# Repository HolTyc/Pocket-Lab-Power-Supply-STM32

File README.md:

# Pocket Lab Power Supply with STM32 MCU

THIS IS A FORK AND THE ORIGINAL VERSION IS HERE: https://github.com/BenMakesEverything/Pocket-Lab-Power-Supply/tree/main
A lab bench power supply, but pocket-sized and battery powered. (This repo is currently WIP)
The main MCU is STM32L031G6U6 for longer battery life.

## What it is:

A 4S Lithium Ion-based Battery Bank which can act as a portable Lab-Bench Power Supply. Designed for use with 4S lithium-ion battery packs.

## Features:

- Adjustable output voltage and current limit
- Battery powered
- USB-C/PD charging
- 0.91 OLED display
- Open hardware and firmware

## Repository Structure:

- `/hardware` - PCB, schematic, BOM, Gerbers, CAD
- `/firmware` - MCU firmware and utilities
- `/docs` - build guide, diagrams, images, notes (WIP)

## Parts List

- Main PCB
- "Backpack" PCB for Display Module
- Display: HCMS-2971 or HCMS-2972 or HCMS-2973 or HCMS-2974 or HCMS-2975
- 4S 21700 Battery with integrated BMS (XH2.54mm connector) [LINK](https://www.foxbuying.com/21700-14-8v-4s1p-4500mah-rechargeable-power-lithium-battery-pack-with-customised-connetor.html)
- Faceplate
- 3D Printable Body
- 4x M3 Threaded Inserts
- 4x M3 Hex-head/socket bolts (16mm threaded portion)
- Plastic cap for button
- Encoder Knob [LINK](https://www.adafruit.com/product/5531)

## Documentation:

For common questions, see the [FAQ](docs/FAQ.md). This is a work in progress and I will add more.

The following flowchart gives an overview of the way the main components are connected.

## Safety Notice:

This project involves lithium-ion batteries and power electronics. Build and use at your own risk.

The PCB was designed for use with 4S battery packs. The BQ25792 will charge the pack up to 16.8V.

IF YOU WANT TO USE ANOTHER CELL CONFIGURATION YOU MUST CHANGE THIS! OTHERWISE THE CELLS WILL BE OVERCHARGED AND DAMAGED!

(Pin 20 "PROG" on the BQ25792 is the thing you need to adjust.)

YOU MUST USE A PACK THAT CONTAINS A BMS! THIS DESIGN DOES NOT INCLUDE ONE.

## License!

This project is licensed under the CERN Open Hardware Licence Version 2 - Strongly Reciprocal, CERN-OHL-S-2.0.

Unless otherwise stated, this applies to all hardware design files, firmware, software utilities, documentation, images, diagrams, CAD files, manufacturing files, and other project files in this repository.

Commercial use is allowed under the terms of the license. The project name, author name, logo, branding, and media identity are not licensed for use in marketing or endorsement without permission.

See `LICENSE.txt` for the full license text.

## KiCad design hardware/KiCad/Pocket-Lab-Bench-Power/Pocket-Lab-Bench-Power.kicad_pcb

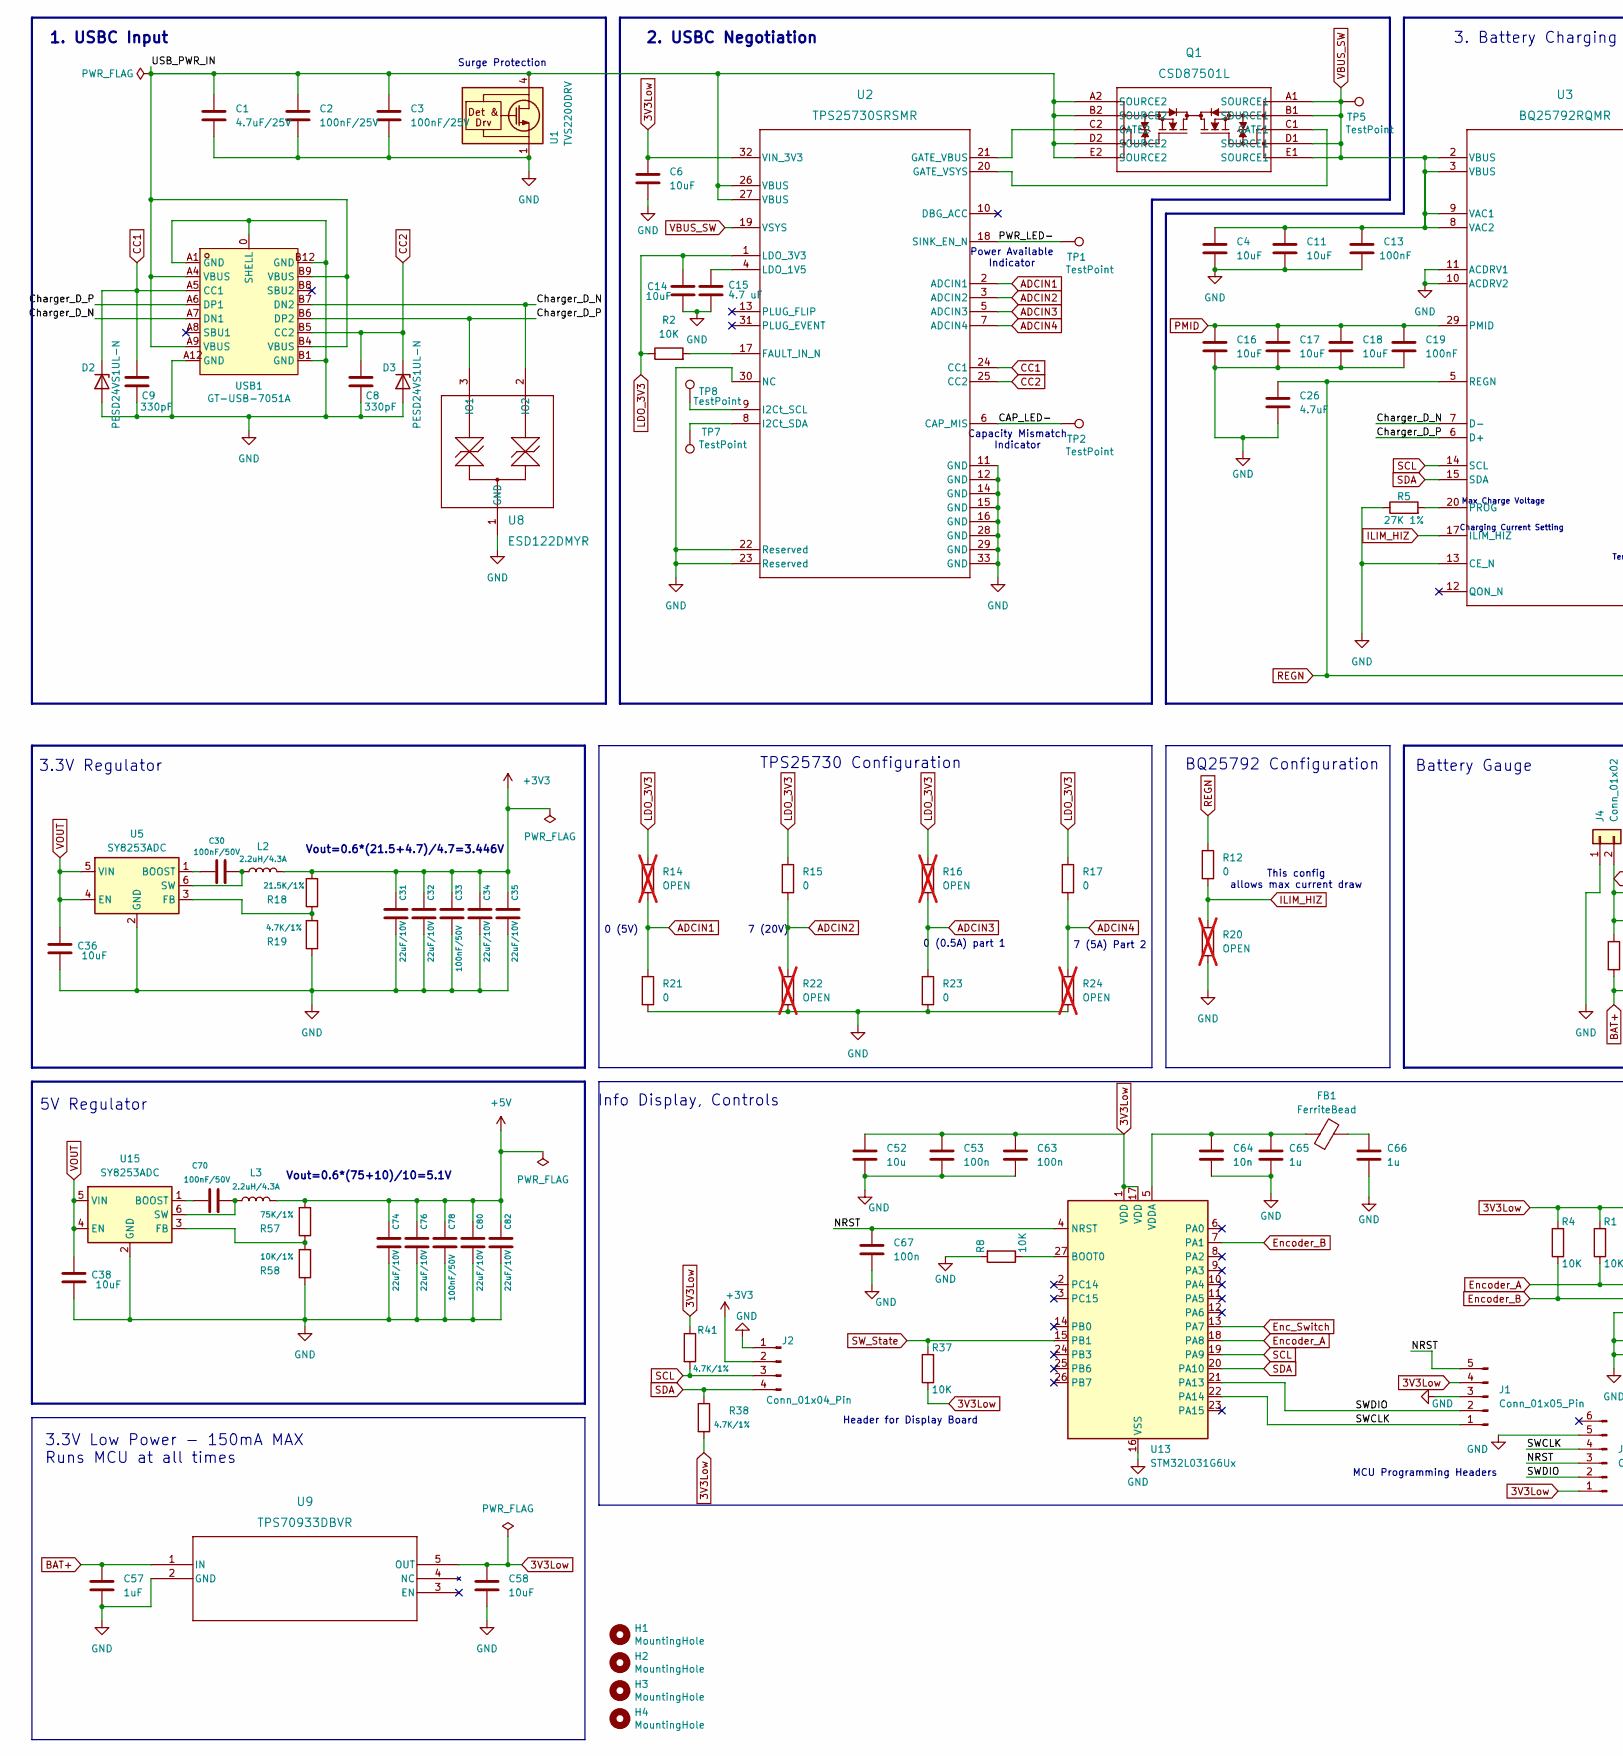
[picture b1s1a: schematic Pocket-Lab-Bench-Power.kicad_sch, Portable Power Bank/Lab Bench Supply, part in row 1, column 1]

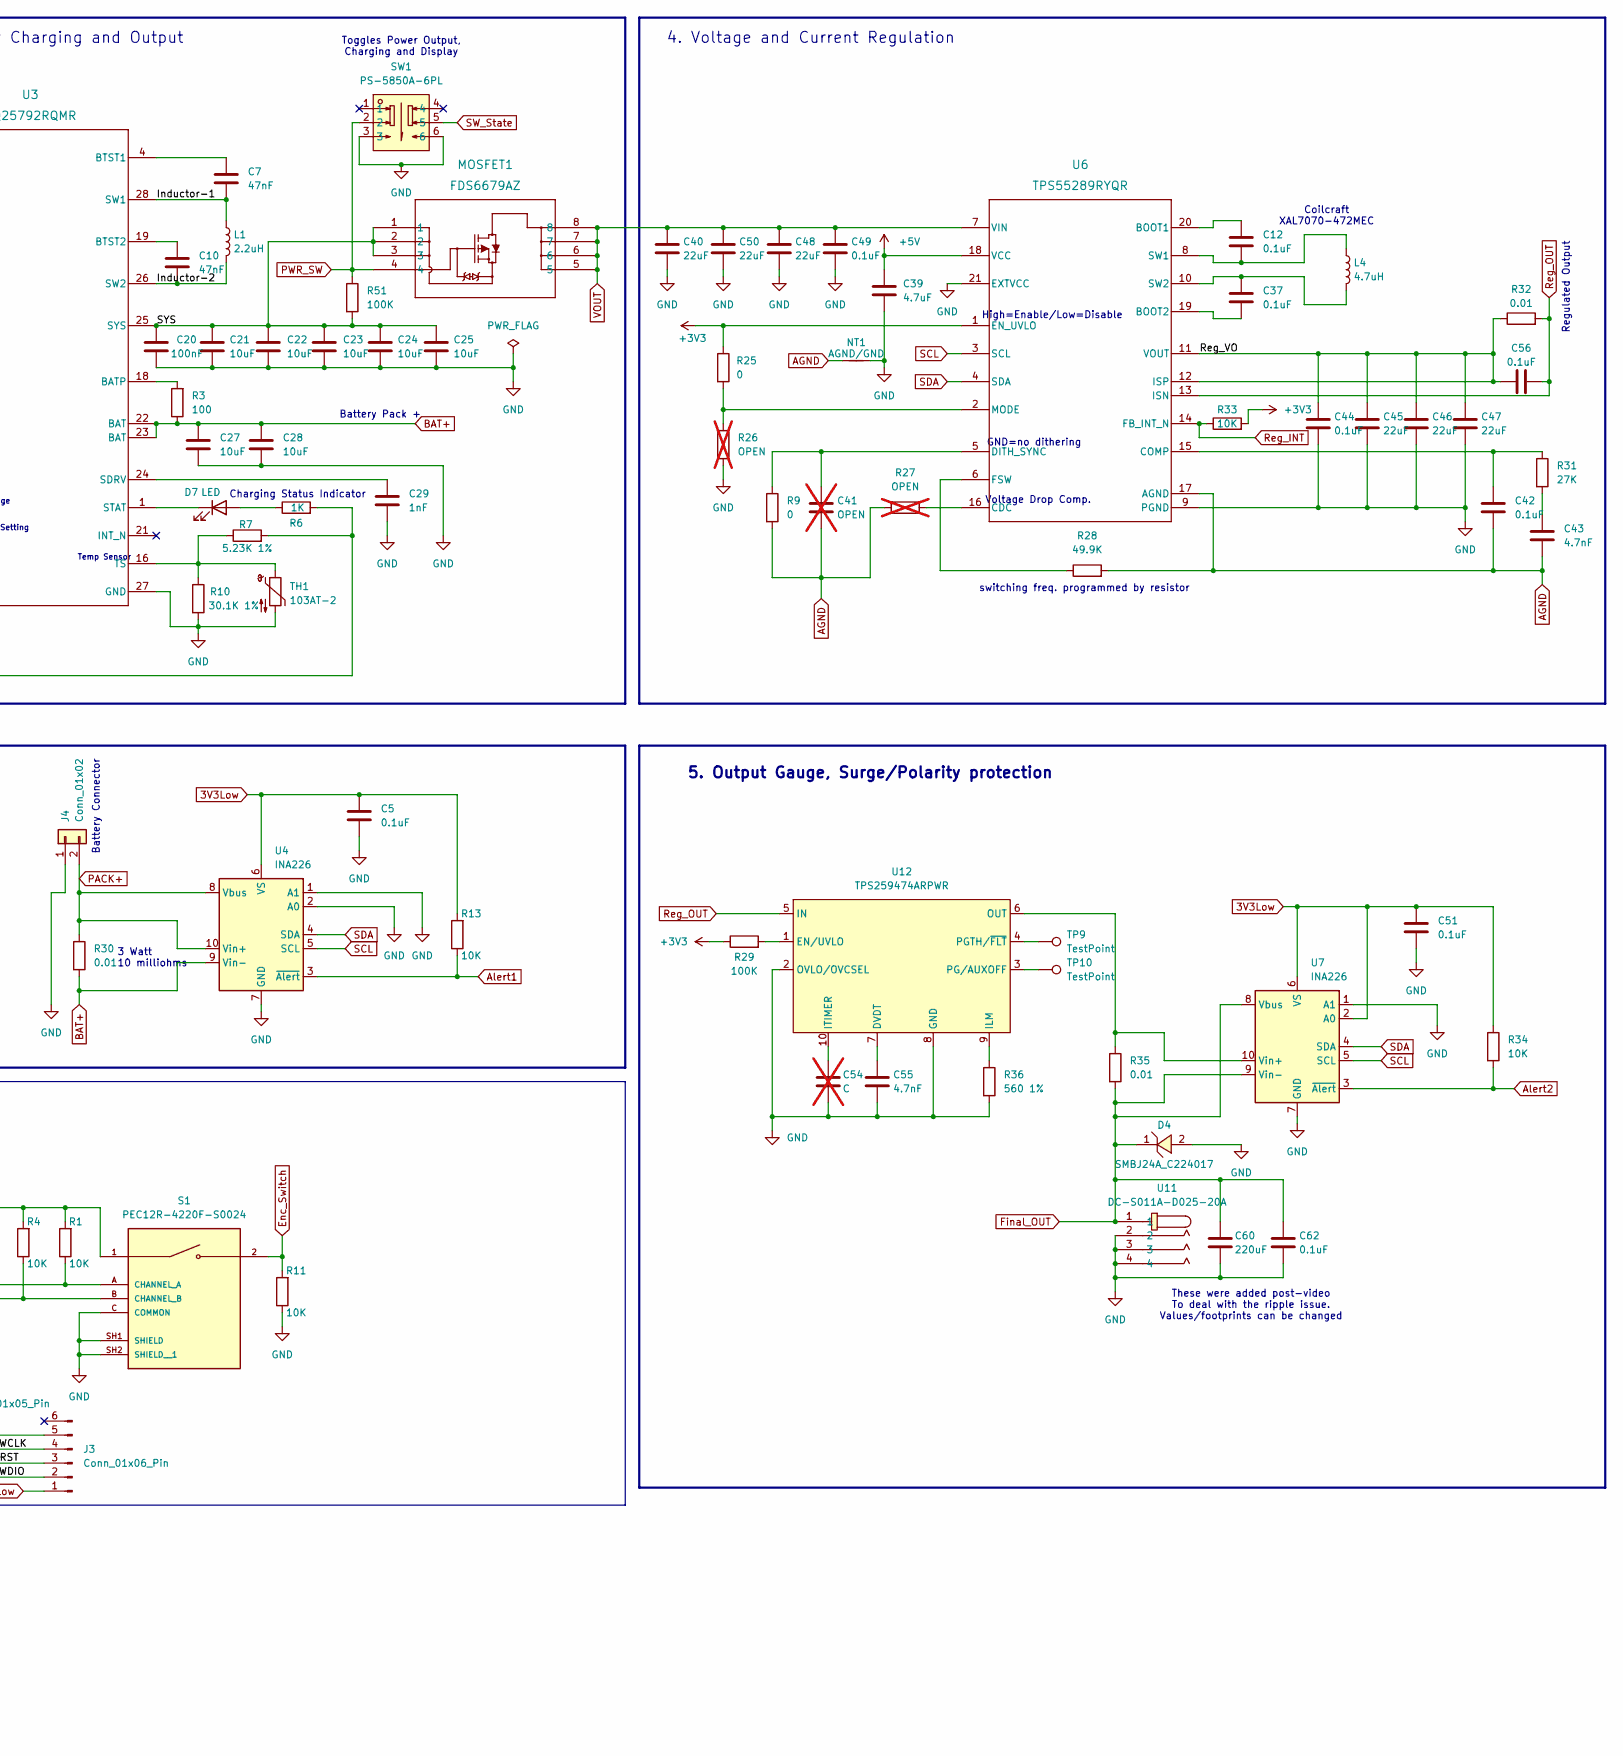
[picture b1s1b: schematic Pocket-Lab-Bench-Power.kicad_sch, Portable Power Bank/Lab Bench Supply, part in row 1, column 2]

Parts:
C1: 4.7uF/25V; C_0603_1608Metric
C2, C3: 100nF/25V; C_0603_1608Metric
C4, C11, C16, C17, C18, C21, C22, C23, C24, C25, C27, C28: 10uF; C_0805_2012Metric
C5, C12, C37, C42, C44, C49, C51, C56: 0.1uF; C_0402_1005Metric
C6, C14, C58: 10uF; C_0402_1005Metric
C7, C10: 47nF; C_0402_1005Metric
C8, C9: 330pF; C_0402_1005Metric
C13, C19, C20: 100nF; C_0402_1005Metric
C15: 4.7 uF; C_0402_1005Metric
C26: 4.7uF; C_0603_1608Metric; Voltage Req 10V
C29: 1nF; C_0402_1005Metric
C30, C33, C70, C78: 100nF/50V; C_0603_1608Metric
C31, C32, C34, C35, C74, C76, C80, C82: 22uF/10V; C_0603_1608Metric
C36, C38: 10uF; C_0603_1608Metric
C39: 4.7uF; C_0603_1608Metric
C40, C45, C46, C47, C48, C50: 22uF; C_0603_1608Metric
C41: OPEN; C_0603_1608Metric; not fitted
C43: 4.7nF; C_0402_1005Metric
C52: 10u; C_0603_1608Metric; LCSC C19702
C53, C63, C67: 100n; C_0402_1005Metric; LCSC C1525
C54: C; C_0603_1608Metric; not fitted
C55: 4.7nF; C_0603_1608Metric
C57: 1uF; C_0603_1608Metric
C60: 220uF; C_1206_3216Metric; LCSC C412252
C62: 0.1uF; C_0603_1608Metric
C64: 10n; C_0402_1005Metric; LCSC C15195
C65, C66: 1u; C_0402_1005Metric; LCSC C52923
D2, D3: PESD24VS1UL-N; DFN1006-2L-RD; LCSC Part C406227
D4: SMBJ24A_C224017; SMB_L4.3-W3.6-LS5.4-RD; MPN SMBJ24A; LCSC Part C224017
D7: LED; LED_0603_1608Metric; LCSC Part C72038
FB1: FerriteBead; L_0603_1608Metric; LCSC C1002
H1, H2, H3, H4: MountingHole; MountingHole_3.2mm_M3
J1: Conn_01x05_Pin; PinHeader_1x05_P2.54mm_Vertical
J2: Conn_01x04_Pin; PinHeader_1x04_P2.54mm_Vertical; LCSC Part C2691448
J3: Conn_01x06_Pin; Edge_Connect_6
J4: Conn_01x02; JST_PH_B2B-PH-K_1x02_P2.00mm_Vertical; LCSC Part C495685
L1: 2.2uH; IND-SMD_L7.0-W6.6_MCW-0650-220; LCSC Part C5349701
L2, L3: 2.2uH/4.3A; L_Sunlord_SWPA4020S; LCSC Part C3222957
L4: 4.7uH; IND-SMD_L7.5-W7.2-1; LCSC Part C3911513
MOSFET1: FDS6679AZ; SOIC8_751EB_ONS; LCSC Part C116730
NT1: AGND/GND; NetTie-2_SMD_Pad0.5mm
Q1: CSD87501L; PICOSTAR-YJG_TEX; LCSC Part C2841784
R1, R4, R8, R11, R13, R37: 10K; R_0402_1005Metric; LCSC C25744
R2, R33, R34: 10K; R_0402_1005Metric
R3: 100; R_0603_1608Metric
R5: 27K 1%; R_0603_1608Metric
R6: 1K; R_0603_1608Metric
R7: 5.23K 1%; R_0603_1608Metric
R9, R12, R15, R17, R21, R23, R25: 0; R_0603_1608Metric
R10: 30.1K 1%; R_0603_1608Metric
R14, R16, R20, R22, R24, R26, R27: OPEN; R_0603_1608Metric; not fitted
R18: 21.5K/1%; R_0603_1608Metric
R19, R38, R41: 4.7K/1%; R_0603_1608Metric
R28: 49.9K; R_0603_1608Metric
R29, R51: 100K; R_0603_1608Metric
R30, R32, R35: 0.01; R_2512_6332Metric; LCSC Part C840621
R31: 27K; R_0402_1005Metric
R36: 560 1%; R_0603_1608Metric
R57: 75K/1%; R_0603_1608Metric
R58: 10K/1%; R_0603_1608Metric
S1: PEC12R-4220F-S0024; XDCR_PEC12R-4220F-S0024; PARTREV 07/21; LCSC Part C18164805
SW1: PS-5850A-6PL; SW-TH_6P-L5.8-W5.8-P2.00-LS4.5-BL_1; MPN PS-5850A-6PL; LCSC Part C963201
TH1: 103AT-2; PinHeader_1x02_P2.54mm_Vertical
TP1, TP2, TP5, TP7, TP8, TP9, TP10: TestPoint; TestPoint_Pad_D1.5mm
U1: TVS2200DRV; WSON-6-1EP_2x2mm_P0.65mm_EP1x1.6mm; LCSC Part C523793
U2: TPS25730SRSMR; RSM0032B-IPC_A; LCSC Part C22390380
U3: BQ25792RQMR; BQ25792; LCSC Part C2862876
U4: INA226; VSSOP-10_3x3mm_P0.5mm
U5, U15: SY8253ADC; TSOT-23-6; LCSC Part C93736
U6: TPS55289RYQR; RYQ0021A-MFG; LCSC Part C5942077
U7: INA226; VSSOP-10_3x3mm_P0.5mm; LCSC Part C49851
U8: ESD122DMYR; DMY0003A; LCSC Part C1975871
U9: TPS70933DBVR; DBV5_TEX; LCSC Part C89347
U11: DC-S011A-D025-20A; AUDIO-TH_DC-S011A-D025-20A; MPN DC-S011A-D025-20A; LCSC Part C7464915
U12: TPS259474ARPWR; VQFN-10_L2.0-W2.0-P0.45-TL; MPN TPS259474ARPWR; LCSC Part C3662807
U13: STM32L031G6Ux; QFN-28_4x4mm_P0.5mm; LCSC C96514
USB1: GT-USB-7051A; USB-C-SMD_GT-USB-7051A; MPN GT-USB-7051A; LCSC Part C2843970

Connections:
3V3Low: C5.1, C6.1, C51.1, C52.1, C53.1, C58.1, C63.1, J1.4, J3.1, R1.2, R4.2, R13.2, R34.1, R37.1, R38.2, R41.1, S1.1, U2.32 (VIN_3V3), U4.6 (VS), U7.2 (A0), U7.6 (VS), U9.5 (OUT), U13.1 (VDD), U13.17 (VDD)
+3V3: C31.2, C32.2, C33.1, C34.2, C35.2, J2.2, L2.2, R18.2, R25.1, R29.1, R33.2, U6.1 (EN_UVLO)
+5V: C39.1, C74.2, C76.2, C78.1, C80.2, C82.2, L3.2, R57.2, U6.18 (VCC)
/CAP_LED-: TP2.1 (1_1), U2.6 (CAP_MIS)
/Charger_D_N: U3.7 (D-), U8.2 (IO2), USB1.A7 (DN1), USB1.B7 (DN2)
/Charger_D_P: U3.6 (D+), U8.3 (IO1), USB1.A6 (DP1), USB1.B6 (DP2)
/Inductor-1: C7.2, L1.1, U3.28 (SW1)
/Inductor-2: C10.2, L1.2, U3.26 (SW2)
/NRST: C67.1, J1.5, J3.3, U13.4 (NRST)
/PWR_LED-: TP1.1 (1_1), U2.18 (SINK_EN_N)
/Reg_VO: C44.1, C45.1, C46.1, C47.1, C56.1, R32.1, U6.11 (VOUT), U6.12 (ISP)
/SWCLK: J1.1, J3.4, U13.22 (PA14)
/SWDIO: J1.2, J3.2, U13.21 (PA13)
/SYS: C20.1, C21.1, C22.1, C23.1, C24.1, C25.1, MOSFET1.1, MOSFET1.2, MOSFET1.3, R51.2, U3.25 (SYS)
/USB_PWR_IN: C1.1, C2.1, C3.1, Q1.A2 (SOURCE2), Q1.B2 (SOURCE2), Q1.D2 (SOURCE2), Q1.E2 (SOURCE2), U1.4 (IN), U1.5 (IN), U1.6 (IN), U2.26 (VBUS), U2.27 (VBUS), USB1.A4 (VBUS), USB1.A9 (VBUS), USB1.B4 (VBUS), USB1.B9 (VBUS)
ADCIN1: R14.2, R21.1, U2.2 (ADCIN1)
ADCIN2: R15.2, R22.1, U2.3 (ADCIN2)
ADCIN3: R16.2, R23.1, U2.5 (ADCIN3)
ADCIN4: R17.2, R24.1, U2.7 (ADCIN4)
AGND: C41.2, C42.2, C43.2, NT1.1, R9.2, R27.1, R28.2, U6.17 (AGND)
Alert1: R13.1, U4.3 (~Alert)
Alert2: R34.2, U7.3 (~Alert)
BAT+: C27.1, C28.1, C57.1, R3.1, R30.2, U3.22 (BAT), U3.23 (BAT), U4.9 (Vin-), U9.1 (IN)
CC1: C9.1, D2.1 (K), U2.24 (CC1), USB1.A5 (CC1)
CC2: C8.1, D3.1 (K), U2.25 (CC2), USB1.B5 (CC2)
Enc_Switch: R11.2, S1.2, U13.13 (PA7)
Encoder_A: R1.1, S1.A (CHANNEL_A), U13.18 (PA8)
Encoder_B: R4.1, S1.B (CHANNEL_B), U13.7 (PA1)
Final_OUT: C60.1, C62.1, D4.1, R35.2, U7.8 (Vbus), U7.9 (Vin-), U11.1
GND: C1.2, C2.2, C3.2, C4.1, C5.2, C6.2, C8.2, C9.2, C11.1, C13.2, C14.2, C15.2, C16.2, C17.2, C18.1, C19.2, C20.2, C21.2, C22.2, C23.2, C24.2, C25.2, C26.2, C27.2, C28.2, C29.2, C31.1, C32.1, C33.2, C34.1, C35.1, C36.2, C38.2, C39.2, C40.2, C44.2, C45.2, C46.2, C47.2, C48.2, C49.2, C50.2, C51.2, C52.2, C53.2, C54.2, C55.2, C57.2, C58.2, C60.2, C62.2, C63.2, C64.2, C65.1, C66.1, C67.2, C74.1, C76.1, C78.2, C80.1, C82.1, D2.2 (A), D3.2 (A), D4.2, J1.3, J2.1, J3.5, J4.1, NT1.2, R5.1, R8.2, R10.2, R11.1, R19.1, R20.2, R21.2, R22.2, R23.2, R24.2, R26.2, R36.2, R58.1, S1.C (COMMON), S1.SH1 (SHIELD), S1.SH2 (SHIELD__1), SW1.3, SW1.6, TH1.2, U1.1 (GND), U1.2 (GND), U1.3 (GND), U1.7 (GND), U2.11 (GND), U2.12 (GND), U2.14 (GND), U2.15 (GND), U2.16 (GND), U2.22 (Reserved), U2.23 (Reserved), U2.28 (GND), U2.29 (GND), U2.30 (NC), U2.33 (GND), U3.10 (ACDRV2), U3.11 (ACDRV1), U3.13 (CE_N), U3.27 (GND), U4.1 (A1), U4.2 (A0), U4.7 (GND), U5.2 (GND), U6.9 (PGND), U6.21 (EXTVCC), U7.1 (A1), U7.7 (GND), U8.1 (GND), U9.2 (GND), U11.2, U11.3, U11.4, U12.2 (OVLO/OVCSEL), U12.8 (GND), U13.16 (VSS), U13.28 (VSS), U15.2 (GND), USB1.0 (SHELL), USB1.A1 (GND), USB1.A12 (GND), USB1.B1 (GND), USB1.B12 (GND)
ILIM_HIZ: R12.2, R20.1, U3.17 (ILIM_HIZ)
LDO_3V3: C14.1, R2.1, R14.1, R15.1, R16.1, R17.1, U2.1 (LDO_3V3)
unnamed: C43.1, R31.2
unnamed: C66.2, FB1.2
unnamed: D7.2 (A), R6.1
unnamed: D7.1 (K), U3.1 (STAT)
unnamed: Q1.C1 (GATE1), U2.20 (GATE_VSYS)
unnamed: Q1.C2 (GATE2), U2.21 (GATE_VBUS)
unnamed: R2.2, U2.17 (FAULT_IN_N)
unnamed: TP8.1 (1_1), U2.9 (I2Ct_SCL)
unnamed: TP7.1 (1_1), U2.8 (I2Ct_SDA)
unnamed: C15.1, U2.4 (LDO_1V5)
unnamed: R3.2, U3.18 (BATP)
unnamed: C7.1, U3.4 (BTST1)
unnamed: C10.1, U3.19 (BTST2)
unnamed: R5.2, U3.20 (PROG)
unnamed: C29.1, U3.24 (SDRV)
unnamed: R7.1, R10.1, TH1.1, U3.16 (TS)
unnamed: C30.2, U5.1 (BOOST)
unnamed: R18.1, R19.2, U5.3 (FB)
unnamed: C30.1, L2.1, U5.6 (SW)
unnamed: C12.1, U6.20 (BOOT1)
unnamed: C37.2, U6.19 (BOOT2)
unnamed: R27.2, U6.16 (CDC)
unnamed: C42.1, R31.1, U6.15 (COMP)
unnamed: C41.1, R9.1, U6.5 (DITH_SYNC)
unnamed: R28.1, U6.6 (FSW)
unnamed: R25.2, R26.1, U6.2 (MODE)
unnamed: C12.2, L4.1, U6.8 (SW1)
unnamed: C37.1, L4.2, U6.10 (SW2)
unnamed: C55.1, U12.7 (DVDT)
unnamed: R29.2, U12.1 (EN/UVLO)
unnamed: R36.1, U12.9 (ILM)
unnamed: C54.1, U12.10 (ITIMER)
unnamed: R35.1, U7.10 (Vin+), U12.6 (OUT)
unnamed: TP9.1 (1_1), U12.4 (PGTH/~FLT)
unnamed: TP10.1 (1_1), U12.3 (PG/AUXOFF)
unnamed: R8.1, U13.27 (BOOT0)
unnamed: C64.1, C65.2, FB1.1, U13.5 (VDDA)
unnamed: C70.2, U15.1 (BOOST)
unnamed: R57.1, R58.2, U15.3 (FB)
unnamed: C70.1, L3.1, U15.6 (SW)
PACK+: J4.2, R30.1, U4.8 (Vbus), U4.10 (Vin+)
PMID: C16.1, C17.1, C18.2, C19.1, U3.29 (PMID)
PWR_SW: MOSFET1.4, R51.1, SW1.2
REGN: C26.1, R6.2, R7.2, R12.1, U3.5 (REGN)
Reg_INT: R33.1, U6.14 (FB_INT_N)
Reg_OUT: C56.2, R32.2, U6.13 (ISN), U12.5 (IN)
SCL: J2.3, R41.2, U3.14 (SCL), U4.5 (SCL), U6.3 (SCL), U7.5 (SCL), U13.19 (PA9)
SDA: J2.4, R38.1, U3.15 (SDA), U4.4 (SDA), U6.4 (SDA), U7.4 (SDA), U13.20 (PA10)
SW_State: R37.2, SW1.5, U13.15 (PB1)
VBUS_SW: C4.2, C11.2, C13.1, Q1.A1 (SOURCE1), Q1.B1 (SOURCE1), Q1.D1 (SOURCE1), Q1.E1 (SOURCE1), TP5.1 (1_1), U2.19 (VSYS), U3.2 (VBUS), U3.3 (VBUS), U3.8 (VAC2), U3.9 (VAC1)
VOUT: C36.1, C38.1, C40.1, C48.1, C49.1, C50.1, MOSFET1.5, MOSFET1.6, MOSFET1.7, MOSFET1.8, U5.4 (EN), U5.5 (VIN), U6.7 (VIN), U15.4 (EN), U15.5 (VIN)

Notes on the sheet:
Info Display, Controls
GND=no dithering
Battery Connector
4. Voltage and Current Regulation
Surge Protection
Voltage Drop Comp.
0 (5V)
switching freq. programmed by resistor
Battery Pack +
Charging Status Indicator
7 (20V)
BQ25792 Configuration
Temp Sensor
3.3V Regulator
Header for Display Board
Coilcraft XAL7070-472MEC
1. USBC Input
2. USBC Negotiation
TPS25730 Configuration
5. Output Gauge, Surge/Polarity protection
Regulated Output
3.3V Low Power - 150mA MAX Runs MCU at all times
3. Battery Charging and Output
7 (5A) Part 2
0 (0.5A) part 1
Capacity Mismatch Indicator
Charging Current Setting
These were added post-video To deal with the ripple issue. Values/footprints can be changed
Power Available Indicator
MCU Programming Headers
This config allows max current draw
Toggles Power Output, Charging and Display
3 Watt 10 milliohms
Max Charge Voltage
5V Regulator
Vout=0.6*(21.5+4.7)/4.7=3.446V
High=Enable/Low=Disable
Battery Gauge
Vout=0.6*(75+10)/10=5.1V

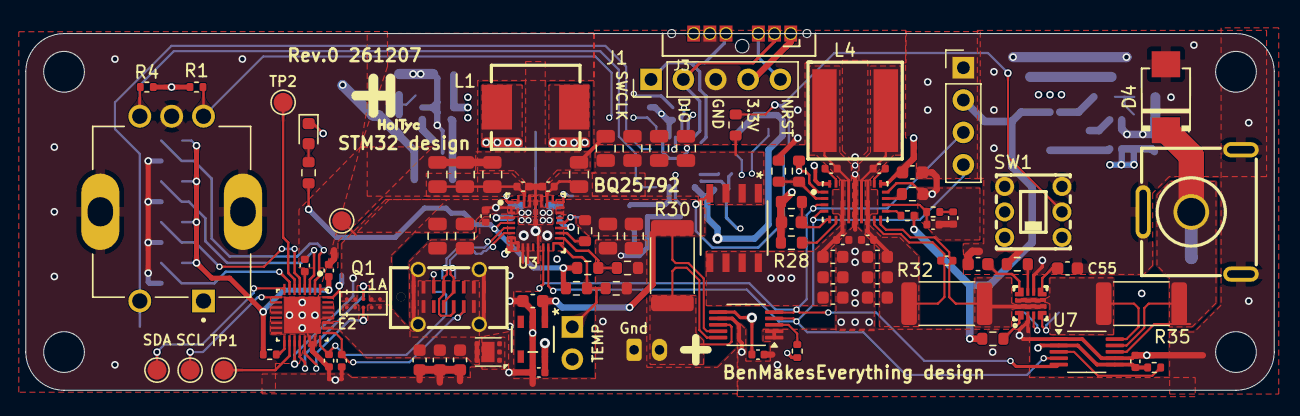
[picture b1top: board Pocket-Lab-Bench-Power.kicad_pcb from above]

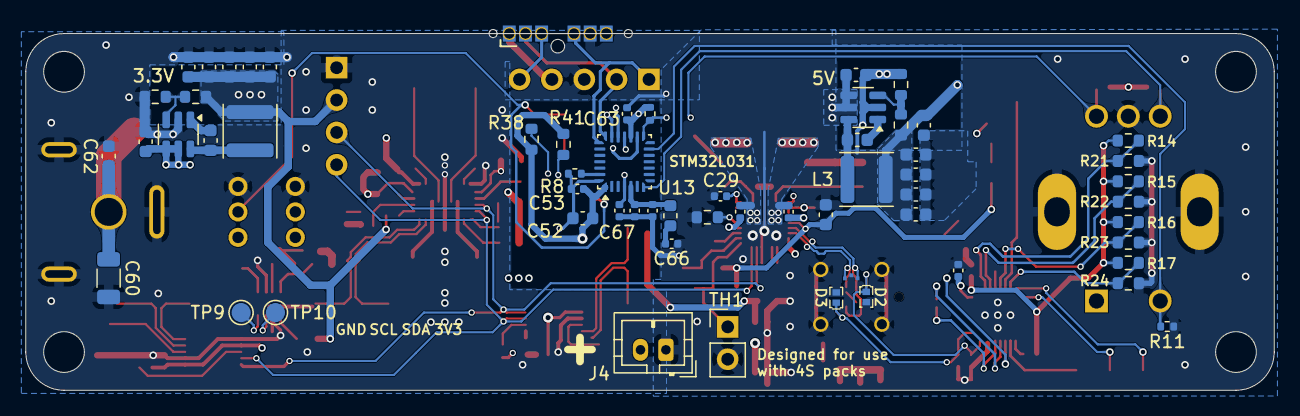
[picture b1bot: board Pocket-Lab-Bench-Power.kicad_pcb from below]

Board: 4 copper layers, 98.0 x 28.0 mm, 157 parts (59 on the bottom side), 83 nets.

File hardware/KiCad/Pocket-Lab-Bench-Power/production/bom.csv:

Designator,Footprint,Quantity,Value,LCSC Part #
C1,0603,1,4.7uF/25V,
"C10, C7",0402,2,47nF,
"C11, C16, C17, C18, C21, C22, C23, C24, C25, C27, C28, C4",0805,12,10uF,
"C12, C37, C42, C44, C49, C5, C51, C56",0402,8,0.1uF,
"C13, C19, C20",0402,3,100nF,
"C14, C58, C6",0402,3,10uF,
C15,0402,1,4.7 uF,
"C2, C3",0603,2,100nF/25V,
"C26, C39",0603,2,4.7uF,
C29,0402,1,1nF,
"C30, C33, C70, C78",0603,4,100nF/50V,
"C31, C32, C34, C35, C74, C76, C80, C82",0603,8,22uF/10V,
"C36, C38",0603,2,10uF,
"C40, C45, C46, C47, C48, C50",0603,6,22uF,
C43,0402,1,4.7nF,
C52,0603,1,10u,C19702
"C53, C63, C67",0402,3,100n,C1525
C55,0603,1,4.7nF,
C57,0603,1,1uF,
C60,1206,1,220uF,C412252
C62,0603,1,0.1uF,
C64,0402,1,10n,C15195
"C65, C66",0402,2,1u,C52923
"C8, C9",0402,2,330pF,
"D2, D3",DFN1006-2L-RD,2,PESD24VS1UL-N,C406227
D4,SMB_L4.3-W3.6-LS5.4-RD,1,SMBJ24A_C224017,C224017
D7,0603,1,LED,C72038
FB1,0603,1,FerriteBead,C1002
J1,PinHeader_1x05_P2.54mm_Vertical,1,Conn_01x05_Pin,
J2,PinHeader_1x04_P2.54mm_Vertical,1,Conn_01x04_Pin,C2691448
J3,Edge_Connect_6,1,Conn_01x06_Pin,
J4,JST_PH_B2B-PH-K_1x02_P2.00mm_Vertical,1,Conn_01x02,C495685
L1,IND-SMD_L7.0-W6.6_MCW-0650-220,1,2.2uH,C5349701
"L2, L3",L_Sunlord_SWPA4020S,2,2.2uH/4.3A,C3222957
L4,IND-SMD_L7.5-W7.2-1,1,4.7uH,C3911513
MOSFET1,SOIC8_751EB_ONS,1,FDS6679AZ,C116730
Q1,PICOSTAR-YJG_TEX,1,CSD87501L,C2841784
"R1, R11, R13, R37, R4, R8",0402,6,10K,C25744
R10,0603,1,30.1K 1%,
"R12, R15, R17, R21, R23, R25, R9",0603,7,0,
R18,0603,1,21.5K/1%,
"R19, R38, R41",0603,3,4.7K/1%,
"R2, R33, R34",0402,3,10K,
R28,0603,1,49.9K,
"R29, R51",0603,2,100K,
R3,0603,1,100,
"R30, R32, R35",2512,3,0.01,C840621
R31,0402,1,27K,
R36,0603,1,560 1%,
R5,0603,1,27K 1%,
R57,0603,1,75K/1%,
R58,0603,1,10K/1%,
R6,0603,1,1K,
R7,0603,1,5.23K 1%,
S1,XDCR_PEC12R-4220F-S0024,1,PEC12R-4220F-S0024,C18164805
SW1,SW-TH_6P-L5.8-W5.8-P2.00-LS4.5-BL_1,1,PS-5850A-6PL,C963201
TH1,PinHeader_1x02_P2.54mm_Vertical,1,103AT-2,
"TP10, TP7, TP8, TP9",TestPoint_Pad_D1.5mm,4,TestPoint,
U1,WSON-6-1EP_2x2mm_P0.65mm_EP1x1.6mm,1,TVS2200DRV,C523793
U11,AUDIO-TH_DC-S011A-D025-20A,1,DC-S011A-D025-20A,C7464915
U12,VQFN-10_L2.0-W2.0-P0.45-TL,1,TPS259474ARPWR,C3662807
U13,QFN-28_4x4mm_P0.5mm,1,STM32L031G6Ux,C96514
"U15, U5",TSOT-23-6,2,SY8253ADC,C93736
U2,RSM0032B-IPC_A,1,TPS25730SRSMR,C22390380
U3,BQ25792,1,BQ25792RQMR,C2862876
U4,VSSOP-10_3x3mm_P0.5mm,1,INA226,
U6,RYQ0021A-MFG,1,TPS55289RYQR,C5942077
U7,VSSOP-10_3x3mm_P0.5mm,1,INA226,C49851
U8,DMY0003A,1,ESD122DMYR,C1975871
U9,DBV5_TEX,1,TPS70933DBVR,C89347
USB1,USB-C-SMD_GT-USB-7051A,1,GT-USB-7051A,C2843970

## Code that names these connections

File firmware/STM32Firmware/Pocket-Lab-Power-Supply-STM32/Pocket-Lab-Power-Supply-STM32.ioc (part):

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Mcu.Name=STM32L031G(4-6)Ux
Mcu.Package=UFQFPN28
Mcu.UserName=STM32L031G6Ux
PA1.Signal=S_TIM2_CH2
PA10.Mode=I2C
PA10.Signal=I2C1_SDA
PA13.Mode=Serial_Wire
PA13.Signal=SYS_SWDIO
PA14.Mode=Serial_Wire
PA14.Signal=SYS_SWCLK
PA7.GPIOParameters=GPIO_Label
PA7.GPIO_Label=SW_State
PA7.Signal=GPIO_Input
PA8.Signal=S_TIM2_CH1
PA9.Mode=I2C
PA9.Signal=I2C1_SCL
PB1.GPIOParameters=GPIO_Label
PB1.GPIO_Label=Enc_switch
PB1.Signal=GPIO_Input
RCC.HSE_VALUE=8000000
RCC.SYSCLKFreq_VALUE=32000000
RCC.SYSCLKSource=RCC_SYSCLKSOURCE_PLLCLK
board=custom
